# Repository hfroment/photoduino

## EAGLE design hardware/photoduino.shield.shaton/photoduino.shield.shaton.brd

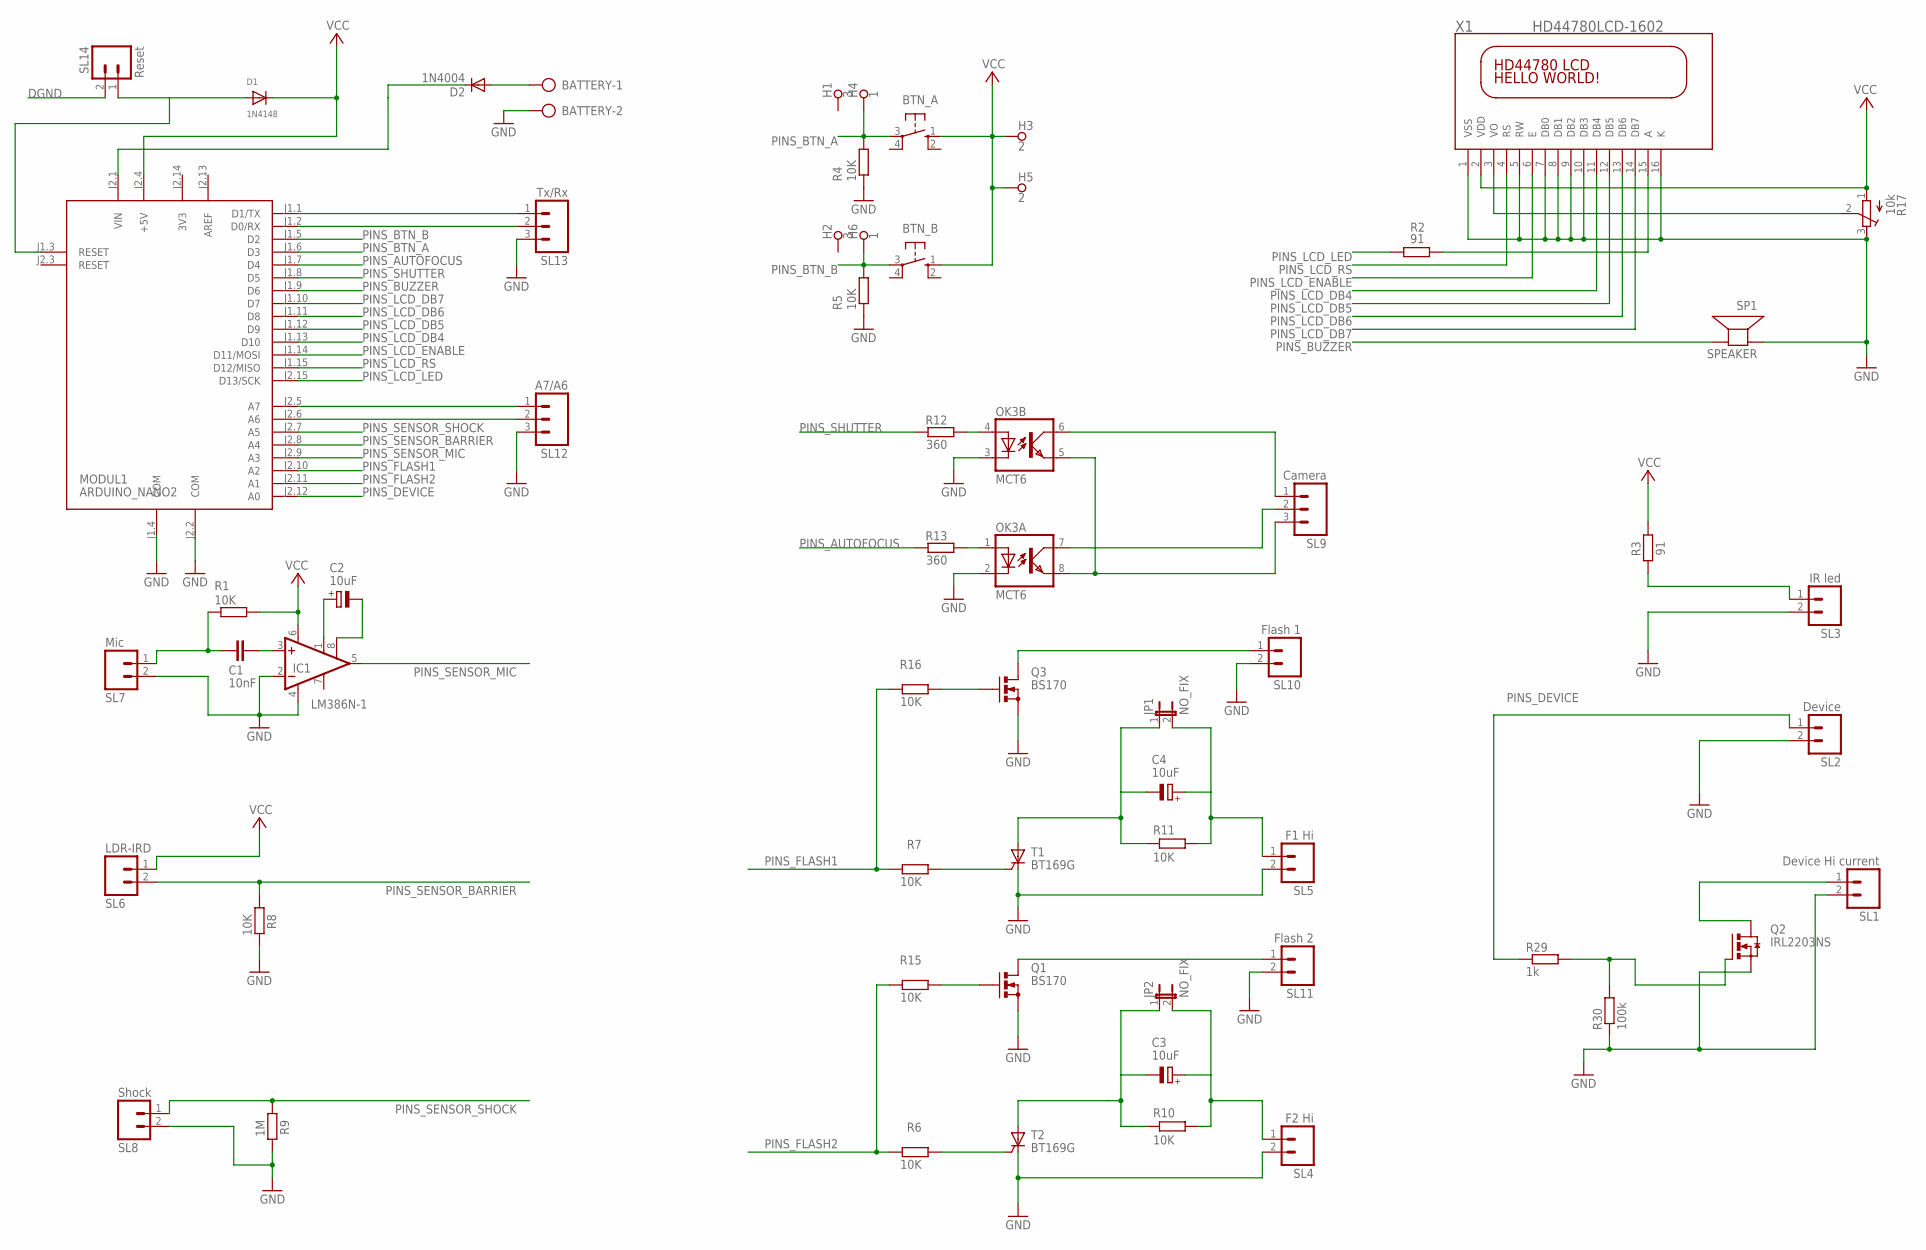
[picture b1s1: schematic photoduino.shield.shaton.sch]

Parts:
BATTERY: AK500/2
BTN_A: 10-XX; B3F-10XX
BTN_B: 10-XX; B3F-10XX
C1: 10nF; C050-025X075
C2, C3, C4: 10uF; E2,5-7
D1: 1N4148; DO-1N4148
D2: 1N4004; DO41-10
H1, H2: 3; PAD_0.1000
H3, H5: 2; PAD_0.1000
H4, H6: 1; PAD_0.1000
IC1: LM386N-1; DIL08
JP1, JP2: NO_FIX; JP1
MODUL1: ARDUINO_NANO2
OK3: MCT6; DIL08
Q1, Q3: BS170; SOT54E
Q2: IRL2203NS; D2PACK
R1, R4, R5, R6, R7, R8, R10, R11, R15, R16: 10K; 0207/7
R2, R3: 91; 0207/7
R9: 1M; 0207/7
R12, R13: 360; 0207/7
R17: 10k; RTRIM64W
R29: 1k; 0207/7
R30: 100k; 0207/7
SL1: Device Hi current; 02P
SL2: Device; 02P
SL3: IR led; 02P
SL4: F2 Hi; 02P
SL5: F1 Hi; 02P
SL6: LDR-IRD; 02P
SL7: Mic; 02P
SL8: Shock; 02P
SL9: Camera; 03P
SL10: Flash 1; 02P
SL11: Flash 2; 02P
SL12: A7/A6; 03P
SL13: Tx/Rx; 03P
SL14: Reset; 02P
SP1: SPEAKER; PS12
T1, T2: BT169G; TO92-2
X1: HD44780LCD-1602; LCD1602

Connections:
3V3: MODUL1.J2.14 (3V3)
AREF: MODUL1.J2.13 (AREF)
DGND: BATTERY.2, IC1.2 (-IN), IC1.4 (GND), MODUL1.J1.4 (COM), MODUL1.J2.2 (COM), OK3.2 (C), OK3.3 (C), Q1.S, Q2.3 (S), Q3.S, R4.1, R5.1, R8.2, R9.2, R17.3 (A), R30.1, SL1.2, SL2.2, SL3.2, SL4.2, SL5.2, SL7.2, SL8.2, SL10.2, SL11.2, SL12.3, SL13.3, SL14.2, SP1.P$1 (+), T1.C, T2.C, X1.1 (VSS), X1.5 (RW), X1.7 (DB0), X1.8 (DB1), X1.9 (DB2), X1.10 (DB3), X1.16 (K)
LCD_CONTRAST: R17.2 (S), X1.3 (VO)
unnamed: R3.2, SL3.1
unnamed: OK3.5 (EMIT), OK3.8 (EMIT), SL9.3
unnamed: C4.+, JP1.2, R11.2, SL5.1
unnamed: R6.1, T2.G
unnamed: D1.A, MODUL1.J1.3 (RESET), SL14.1
unnamed: C4.-, JP1.1, R11.1, T1.A
unnamed: Q2.1 (G), R29.2, R30.2
unnamed: C3.+, JP2.2, R10.2, SL4.1
unnamed: C3.-, JP2.1, R10.1, T2.A
unnamed: Q3.G, R16.1
unnamed: D2.C, MODUL1.J2.1 (VIN)
unnamed: C1.1, IC1.3 (+IN)
unnamed: BATTERY.1, D2.A
unnamed: MODUL1.J1.1 (D1/TX), SL13.1
unnamed: Q1.G, R15.1
unnamed: C1.2, R1.1, SL7.1
unnamed: Q3.D, SL10.1
unnamed: R7.1, T1.G
unnamed: Q1.D, SL11.1
unnamed: MODUL1.J1.2 (D0/RX), SL13.2
unnamed: OK3.6 (COL), SL9.1
unnamed: MODUL1.J2.5 (A7), SL12.1
unnamed: OK3.4 (A), R12.1
unnamed: MODUL1.J2.6 (A6), SL12.2
unnamed: OK3.1 (A), R13.1
unnamed: C2.+, IC1.1 (GAIN)
unnamed: Q2.2 (D), SL1.1
unnamed: C2.-, IC1.8 (GAIN)
unnamed: R2.1, X1.15 (A)
PINS_AUTOFOCUS: MODUL1.J1.7 (D4), R13.2
PINS_BTN_A: BTN_A.3, H4.1, MODUL1.J1.6 (D3), R4.2
PINS_BTN_B: BTN_B.3, H6.1, MODUL1.J1.5 (D2), R5.2
PINS_BUZZER: MODUL1.J1.9 (D6), SP1.P$2 (-)
PINS_DEVICE: MODUL1.J2.12 (A0), R29.1, SL2.1
PINS_FLASH1: MODUL1.J2.10 (A2), R7.2, R16.2
PINS_FLASH2: MODUL1.J2.11 (A1), R6.2, R15.2
PINS_LCD_DB4: MODUL1.J1.13 (D10), X1.11 (DB4)
PINS_LCD_DB5: MODUL1.J1.12 (D9), X1.12 (DB5)
PINS_LCD_DB6: MODUL1.J1.11 (D8), X1.13 (DB6)
PINS_LCD_DB7: MODUL1.J1.10 (D7), X1.14 (DB7)
PINS_LCD_ENABLE: MODUL1.J1.14 (D11/MOSI), X1.6 (E)
PINS_LCD_LED: MODUL1.J2.15 (D13/SCK), R2.2
PINS_LCD_RS: MODUL1.J1.15 (D12/MISO), X1.4 (RS)
PINS_SENSOR_BARRIER: MODUL1.J2.8 (A4), R8.1, SL6.2
PINS_SENSOR_MIC: IC1.5 (OUT), MODUL1.J2.9 (A3)
PINS_SENSOR_SHOCK: MODUL1.J2.7 (A5), R9.1, SL8.1
PINS_SHUTTER: MODUL1.J1.8 (D5), R12.2
SHUTTER: OK3.7 (COL), SL9.2
VCC: BTN_A.1 (S), BTN_B.1 (S), D1.C, H3.1, H5.1, IC1.6 (VS), MODUL1.J2.4 (+5V), R1.2, R3.1, R17.1 (E), SL6.1, X1.2 (VDD)

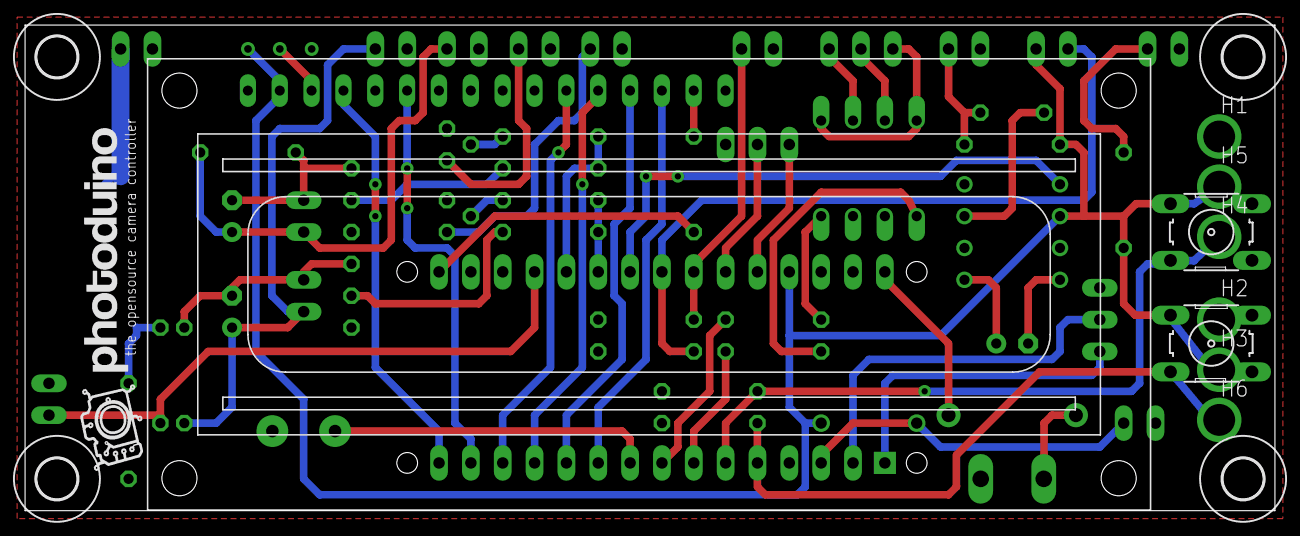
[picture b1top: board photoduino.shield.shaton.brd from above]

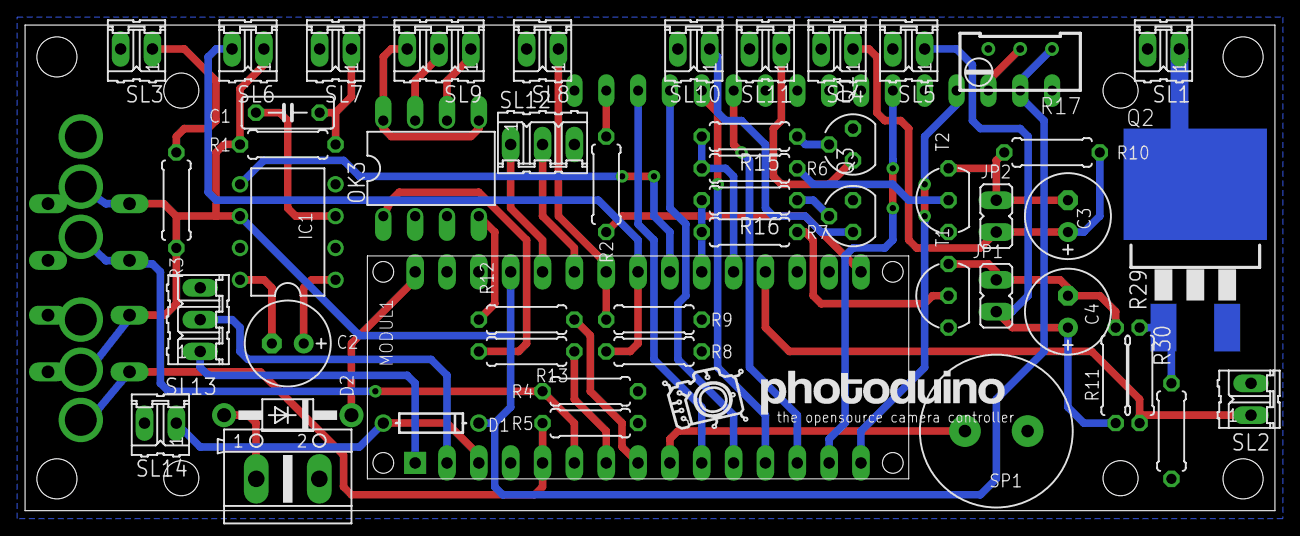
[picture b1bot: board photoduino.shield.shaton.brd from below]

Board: 2 copper layers, 99.7 x 38.7 mm, 65 parts (51 on the bottom side), 51 nets.

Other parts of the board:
U$1, U$2: LOGOPHOTODUINO2
U$3, U$4, U$5, U$6: 3,2

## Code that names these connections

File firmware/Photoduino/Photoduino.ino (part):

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#define LCD_ROWS             2  // rows

// Pinout settings
#define PINS_LCD_LED         13 //(digital pin)
#define PINS_LCD_RS          12 //(digital pin)
#define PINS_LCD_ENABLE      11 //(digital pin)
#define PINS_LCD_DB4         10 //(digital pin)
#define PINS_LCD_DB5         9  //(digital pin)
#define PINS_LCD_DB6         8  //(digital pin)
#define PINS_LCD_DB7         7  //(digital pin)
#define PINS_BUZZER          6  //(digital pin with pwm)
#define PINS_SHUTTER         5  //(digital pin)
#define PINS_AUTOFOCUS       4  //(digital pin)
#define PINS_BTN_A           3  //(digital pin)
#define PINS_BTN_B           2  //(digital pin)

#define PINS_SENSOR_SHOCK    5  //(analog pin)
#define PINS_SENSOR_BARRIER  4  //(analog pin)
#define PINS_SENSOR_MIC      3  //(analog pin)

#ifdef BOARD_ARDUINO_MEGA    // For ArduinoMega compatibility
  #define PINS_FLASH1        56 // Mega pin 56 = Duemilanove 16 (digital pin)
  #define PINS_FLASH2        55 // Mega pin 55 = Duemilanove 15 (digital pin)
  #define PINS_DEVICE        54 // Mega pin 54 = Duemilanove 14 (digital pin)
#else  
  #define PINS_FLASH1        16 //(digital pin)
  #define PINS_FLASH2        15 //(digital pin)
  #define PINS_DEVICE        14 //(digital pin)
#endif

#define PINS_LASER           PINS_DEVICE  // alias(digital pin)
#define PINS_SOLENOID_VALVE  PINS_DEVICE  // alias(digital pin)

// Sensor types
#define SENSOR_TYPE_NONE                 0 // None sensor
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#include LANGUAGE_FILE     // Messages

// LiquidCrystal LCD control object instance
LiquidCrystal lcd(PINS_LCD_RS, PINS_LCD_ENABLE, PINS_LCD_DB4, PINS_LCD_DB5, PINS_LCD_DB6, PINS_LCD_DB7);

// Variables used on interrupt mode
volatile boolean cancelFlag = false;    // Flag used to abort interrupt mode
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  lcd.createChar(SYMBOL_UP, char_arrow_up);

  // Pinmode inputs
  pinMode(PINS_BTN_A,          INPUT);     
  pinMode(PINS_BTN_B,          INPUT);    
  pinMode(PINS_SENSOR_SHOCK,   INPUT); 
  pinMode(PINS_SENSOR_BARRIER, INPUT);
  pinMode(PINS_SENSOR_MIC,     INPUT);  

  // Pinmode outputs
  pinMode(PINS_SHUTTER,        OUTPUT);
  pinMode(PINS_AUTOFOCUS,      OUTPUT);
  pinMode(PINS_FLASH1,         OUTPUT);
  pinMode(PINS_FLASH2,         OUTPUT);
  pinMode(PINS_LCD_LED,        OUTPUT);
  pinMode(PINS_LCD_RS,         OUTPUT);
  pinMode(PINS_LCD_ENABLE,     OUTPUT);
  pinMode(PINS_LCD_DB4,        OUTPUT);
  pinMode(PINS_LCD_DB5,        OUTPUT);
  pinMode(PINS_LCD_DB6,        OUTPUT);
  pinMode(PINS_LCD_DB7,        OUTPUT);
  pinMode(PINS_BUZZER,         OUTPUT);
  pinMode(PINS_DEVICE,         OUTPUT);
  
  // Init Firmata 
  FirmataLite.attach(START_SYSEX, sysexCallback);
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
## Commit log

2015-07-03 French language and prog_char compatibility mod.
2017-01-16 Typo
2017-01-17 New layout. Hi current mosfet for device outpout. Small mosfet for flash outpout. Not tested, but seems to work with official firmware.

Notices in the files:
firmware/Photoduino/Photoduino.ino:
Photoduino is free software: you can redistribute it and/or modify
it under the terms of the GNU General Public License as published by
the Free Software Foundation, either version 3 of the License, or
(at your option) any later version.
